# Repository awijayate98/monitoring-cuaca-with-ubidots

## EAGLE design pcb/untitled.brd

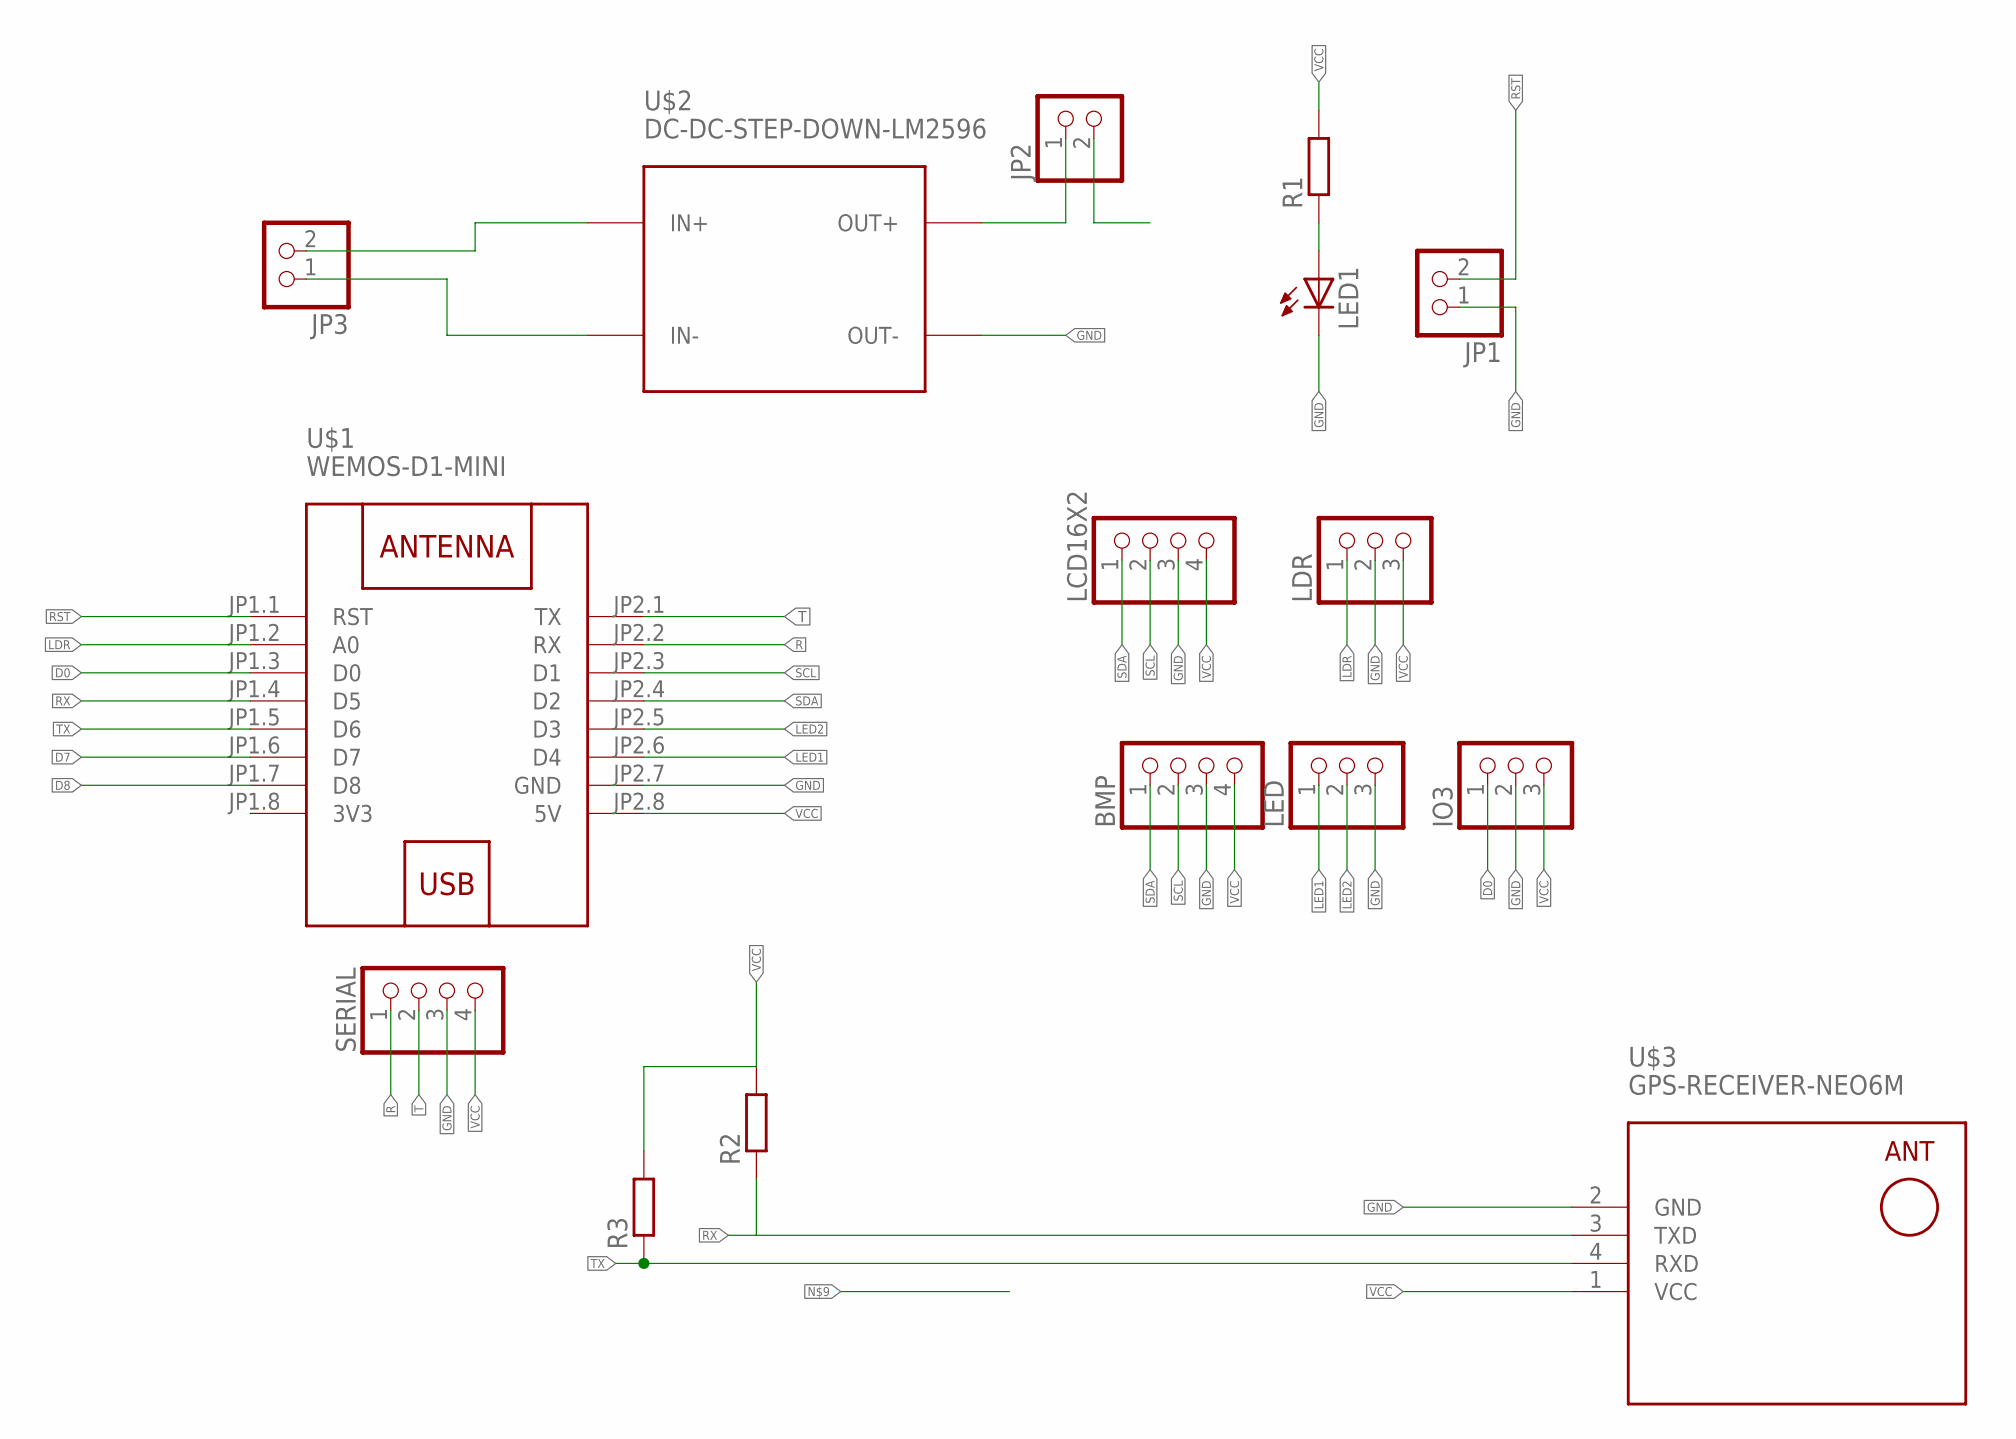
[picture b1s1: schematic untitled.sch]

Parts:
BMP: PINHD-1X4; 1X04
IO3: PINHD-1X3; 1X03
JP1, JP2, JP3: PINHD-1X2; 1X02
LCD16X2: PINHD-1X4; 1X04
LDR: PINHD-1X3; 1X03
LED: PINHD-1X3; 1X03
LED1: LED5MM
R1, R2, R3: R-EU_0204/7; 0204/7
SERIAL: PINHD-1X4; 1X04
U$1: WEMOS-D1-MINI
U$2: DC-DC-STEP-DOWN-LM2596
U$3: GPS-RECEIVER-NEO6M

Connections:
3V3: U$1.JP1.8 (3V3)
D0: IO3.1, U$1.JP1.3 (D0)
D7: U$1.JP1.6 (D7)
D8: U$1.JP1.7 (D8)
GND: BMP.3, IO3.2, JP1.1, LCD16X2.3, LDR.2, LED.3, LED1.K (C), SERIAL.3, U$1.JP2.7 (GND), U$2.OUT-, U$3.2 (GND)
LDR: LDR.1, U$1.JP1.2 (A0)
LED1: LED.1, U$1.JP2.6 (D4)
LED2: LED.2, U$1.JP2.5 (D3)
unnamed: JP3.1, U$2.IN-
unnamed: JP3.2, U$2.IN+
unnamed: JP2.1, U$2.OUT+
unnamed: LED1.A, R1.1
R: SERIAL.1, U$1.JP2.2 (RX)
RST: JP1.2, U$1.JP1.1 (RST)
RX: R2.1, U$1.JP1.4 (D5), U$3.3 (TXD)
SCL: BMP.2, LCD16X2.2, U$1.JP2.3 (D1)
SDA: BMP.1, LCD16X2.1, U$1.JP2.4 (D2)
T: SERIAL.2, U$1.JP2.1 (TX)
TX: R3.1, U$1.JP1.5 (D6), U$3.4 (RXD)
VCC: BMP.4, IO3.3, JP2.2, LCD16X2.4, LDR.3, R1.2, R2.2, R3.2, SERIAL.4, U$1.JP2.8 (5V), U$3.1 (VCC)

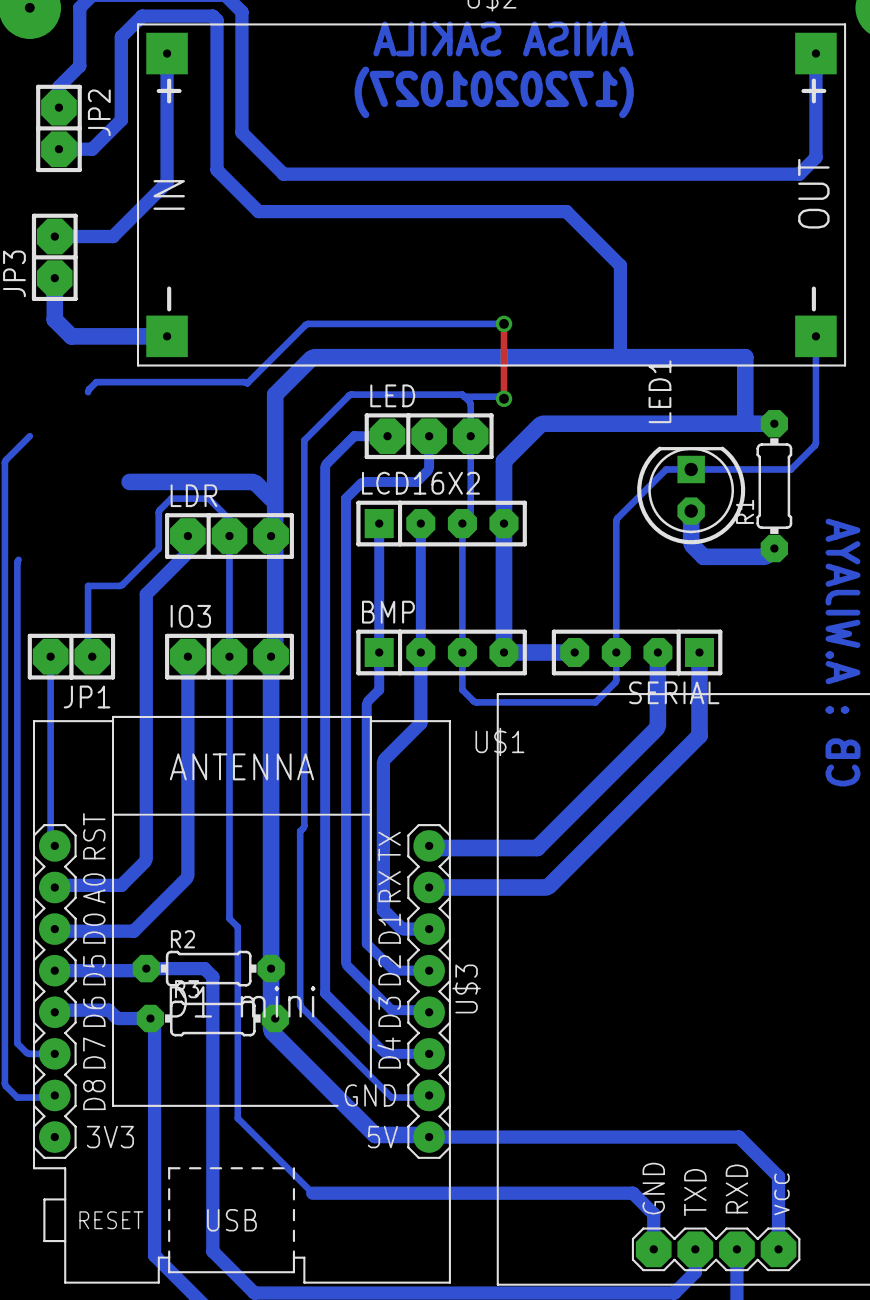
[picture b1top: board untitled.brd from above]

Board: 2 copper layers, 16 parts (0 on the bottom side), 17 nets.

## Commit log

2023-04-26 first cormmit

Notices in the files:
parts and their libraries:
diy-modules: Released under the Creative Commons Attribution 4.0 International License: http://creativecommons.org/licenses/by/4.0
